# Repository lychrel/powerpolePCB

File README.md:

# powerpolePCB
power distribution board for (45A) Anderson PowerPoles (for NCSU's Aerial Robotics Club)

<div style="text-align:center;">

</div>

### Notes:
- if you run standard DRC on a board using the ARC2 package, it'll give dimension errors. This is because ARC2 creates plated slots by laying copper over a dimension rectangle with a drill hit in the middle. This is the [OSHPark](https://oshpark.com/) way of doing it; the ARC package (3POLE variant "OLD") uses a more common plated-slot design. 
- Trace widths pictured for 10A max supply current.
- I forgot mounting holes, though they're easy to add (or just drill manually)
- Eventually I plan on expanding this to a library of packages for the many different ways and configurations in which you can attach the different-size PowerPoles to a PCB.

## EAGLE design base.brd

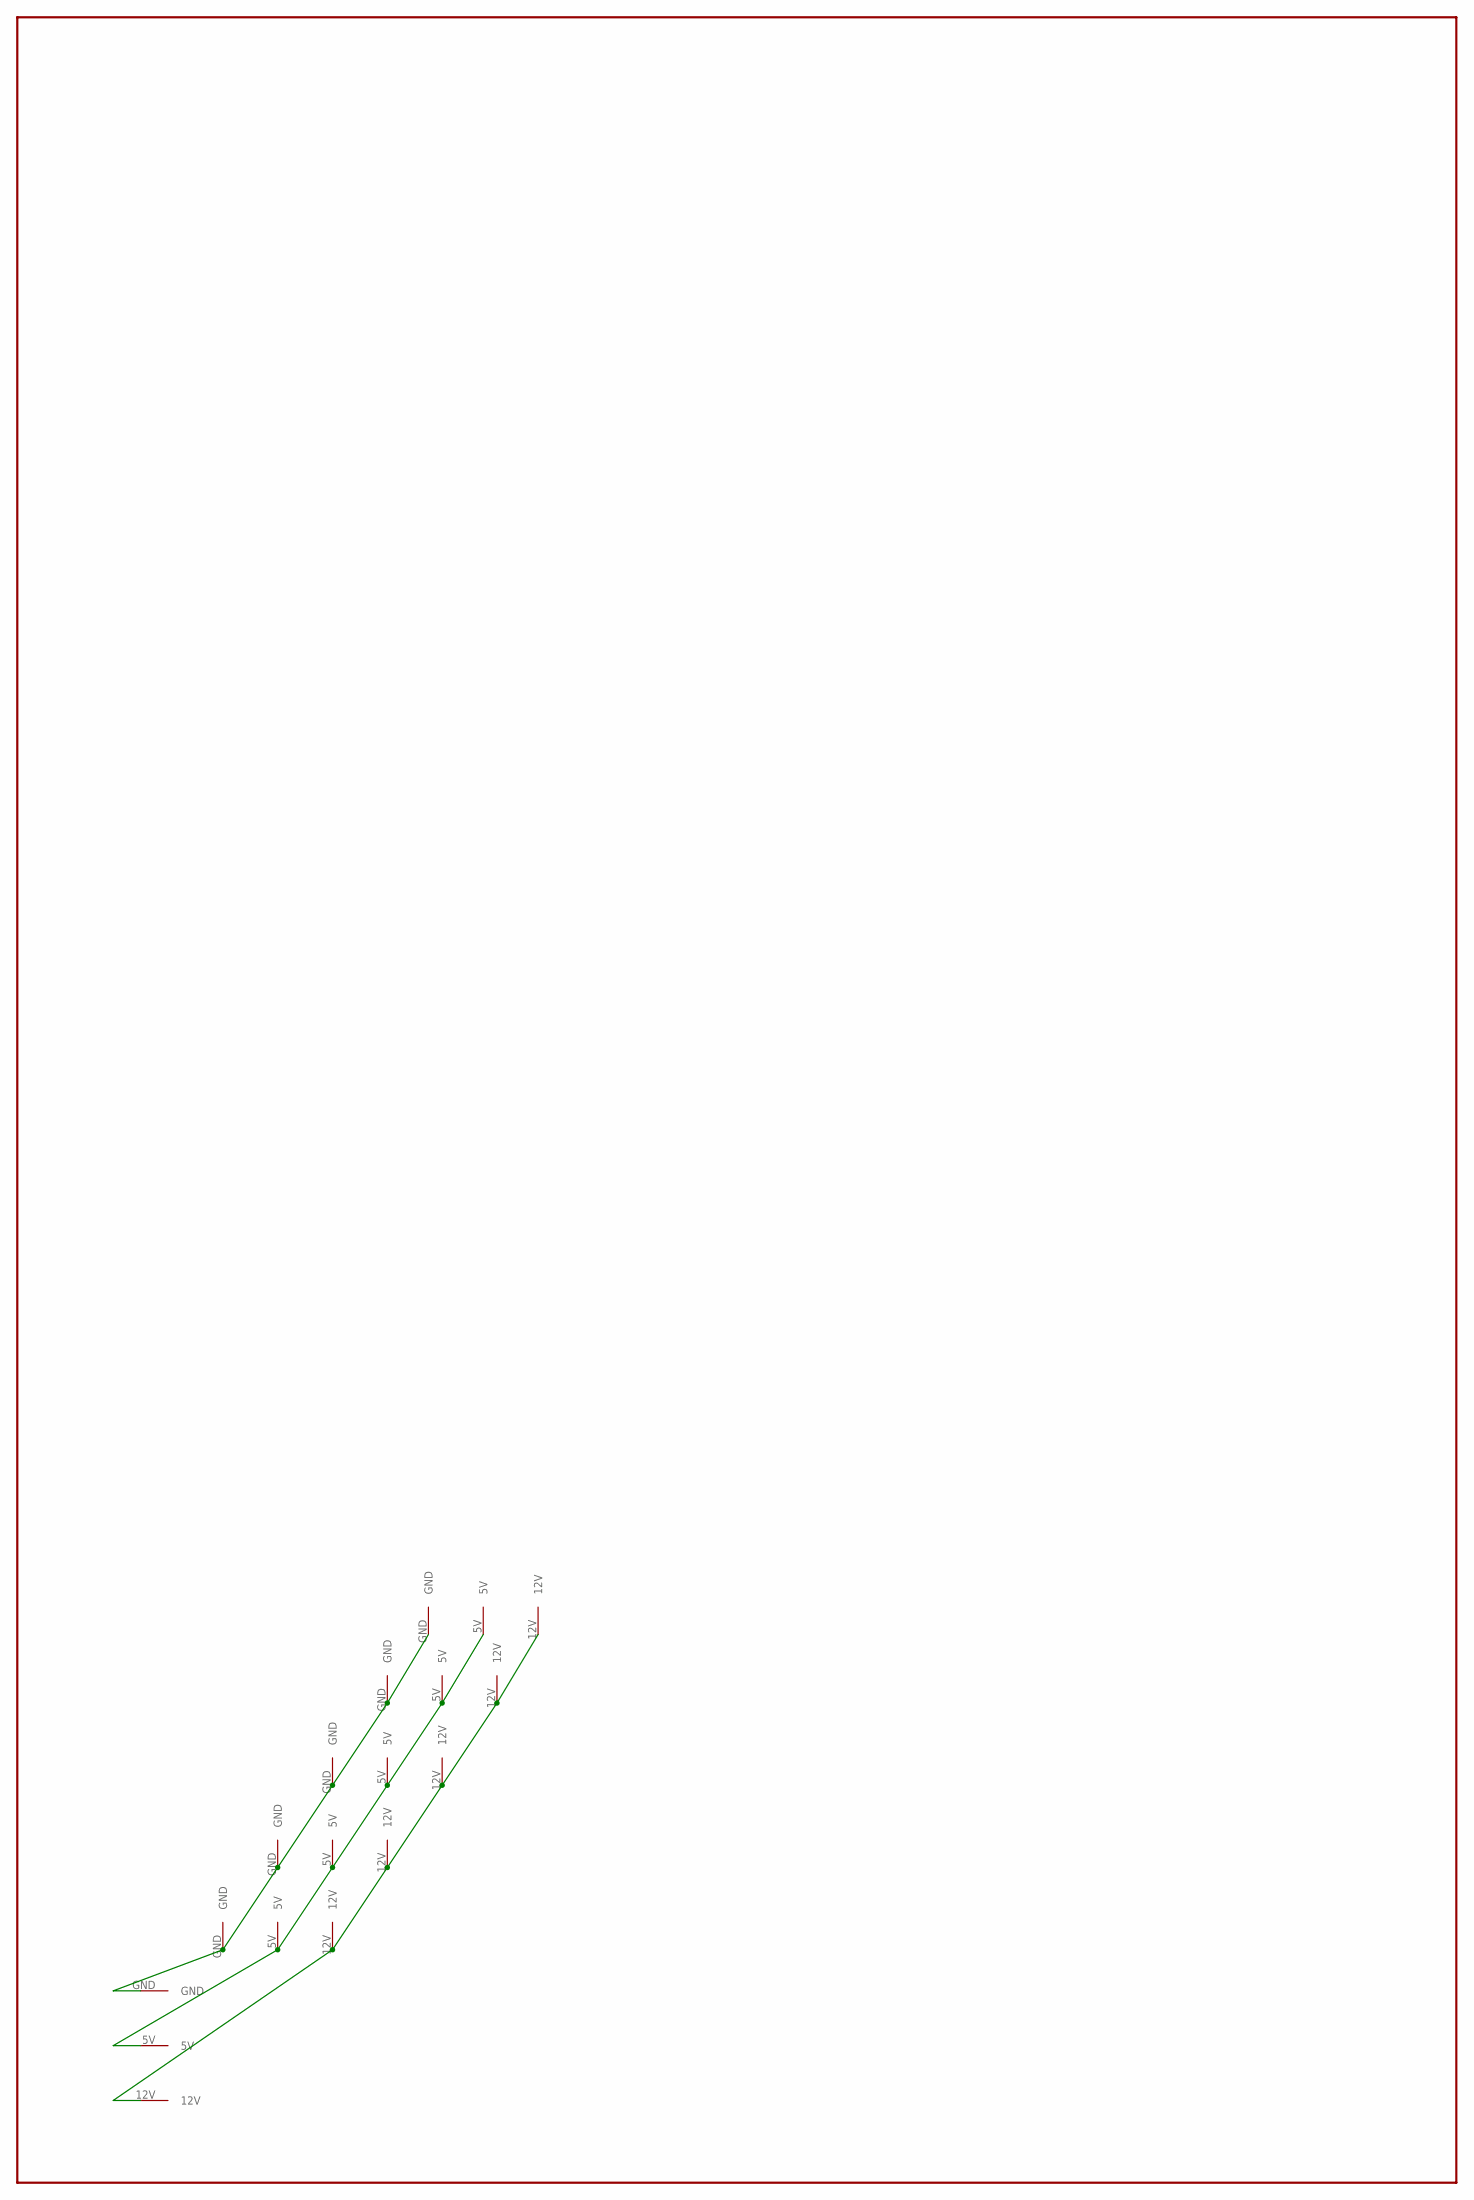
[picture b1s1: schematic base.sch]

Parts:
U$1, U$2, U$3, U$4, U$5, U$6: 3POLE; ARC2

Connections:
5V: U$1.5V, U$2.5V, U$3.5V, U$4.5V, U$5.5V, U$6.5V
12V: U$1.12V, U$2.12V, U$3.12V, U$4.12V, U$5.12V, U$6.12V
GND: U$1.GND, U$2.GND, U$3.GND, U$4.GND, U$5.GND, U$6.GND

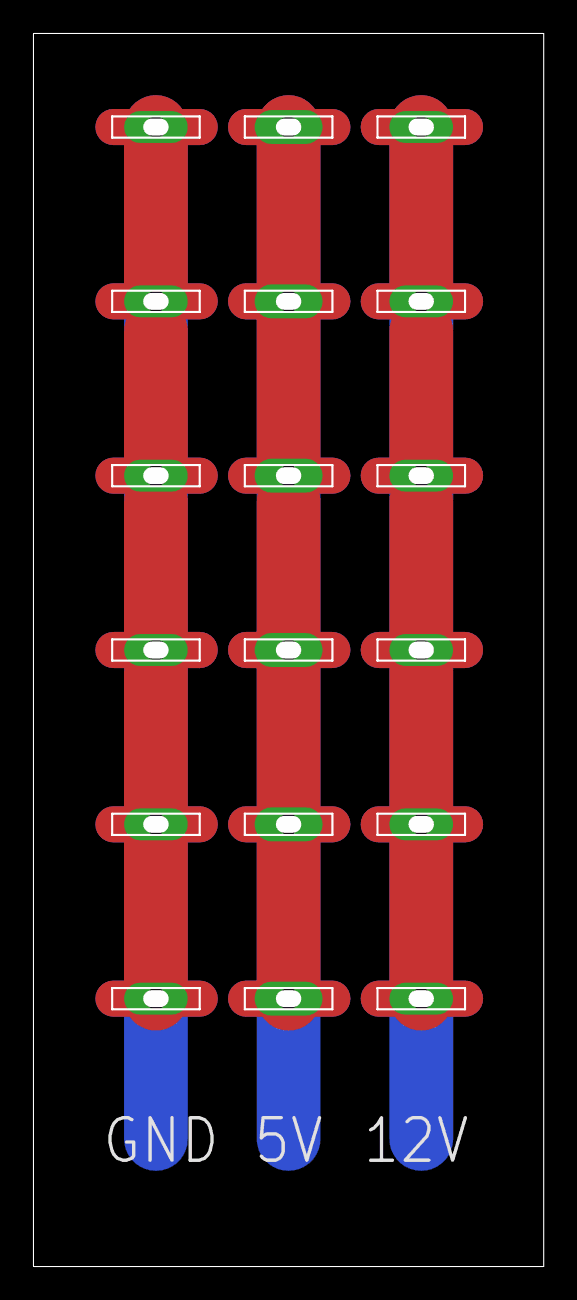
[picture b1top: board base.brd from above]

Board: 2 copper layers, 29.5 x 72.6 mm, 6 parts (0 on the bottom side), 3 nets.

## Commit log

2017-03-16 added BRD
2017-03-16 actually added BRD
2017-03-16 added erroneous ARC2 package png
2017-03-16 added board png
2017-03-16 fixed package outline in tDocu layer
2017-03-17 changed trace widths to accomodate 10A supply
2017-03-17 added copper to bottom layer for plated slots
2017-03-17 linked missing powerpole set, corrected physical mount footprint
2017-03-17 split traces between top and bottom copper to reduce trace width
2017-03-17 corrected slot widths (4mil error)
2017-03-17 fixed README.md oopsie
2017-03-18 tweaked soldermask and silkscreen
2017-03-18 Added 'NCSU ARC' to bottom
2017-03-18 added 3D renderings
2017-03-18 cropped render images
2017-03-18 renamed stl file
2017-03-18 organized images into subdirectories
2017-03-18 made 10-mil correction to PowerPole row placements
2017-03-18 re-rendered board
2017-03-18 added HTML formatting in README.md
2017-03-18 removed air wires from GND and 12V rails (#2)
2017-03-18 replaced board img
2017-03-18 fixed board img issue
2017-03-19 Extended bottom traces to solder on wires
2017-03-20 Updated rendered images
2017-03-30 Edited README.md
